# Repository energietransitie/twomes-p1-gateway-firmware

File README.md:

# Twomes P1 Gateway measurement device
Firmware for the Twomes P1 Gateway measurement device.

## Table of contents
* [General info](#general-info)
* [Deploying](#deploying)
* [Pairing satellites](#pairing-satellites) 
* [Developing](#developing)
* [Features](#features)
* [Status](#status)
* [License](#license)
* [Citation](#citation)
* [Credits](#credits)

## General info
This repository contains the firmware for the [Twomes P1 Gateway device](https://github.com/energietransitie/twomes-p1-gateway-hardware). It is written in C and is based on the [ESP-IDF](https://github.com/espressif/esp-idf) platform. It uses the [Generic Firmware for Twomes measurement devices](https://github.com/energietransitie/twomes-generic-esp-firmware) for matters such as device preperation, provisioning of home Wi-Fi network credentials, device-backend activation, network time synchronisation via NTP and secure uploading of measurement data. 

This specific firmware reads data from the P1 port of smart meters adhering to the [DSMR standards](https://www.netbeheernederland.nl/dossiers/slimme-meter-15/documenten). As part of its gateway function, it can be paired with one or more 'satellite' measurement devices, receive measurements via the energy-efficient [ESP-NOW](https://www.espressif.com/en/products/software/esp-now/overview) protocol, thus lengthening the battery life of such satellite measurement devcies, and upload these messages via Wi-Fi and the internet to a Twomes server.

For the associated hardware design files for the P1 Gateway hardware and enclosure and tips and instructions how to produce and assemble the hardware, please see the [twomes-p1-gateway-hardware](https://github.com/energietransitie/twomes-p1-gateway-hardware) repository. 

## Deploying
This section describes how you can deploy binary releases of the firmware, i.e. without changing the source code, without a development environment and without needing to compile the source code.

### Prerequisites
To deploy the firmware, in addition to the [generic prerequisites for deploying Twomes firmware](https://github.com/energietransitie/twomes-generic-esp-firmware#prerequisites), you need:
* a 3.3V TTL-USB Serial Port Adapter (e.g. [FT232RL](https://www.tinytronics.nl/shop/en/communication-and-signals/usb/ft232rl-3.3v-5v-ttl-usb-serial-port-adapter), CP210x, etc..), including the cable to connect ths adapter to a free USB port on your computer (a USB to miniUSB cable in the case of a [FT232RL](https://www.tinytronics.nl/shop/en/communication-and-signals/usb/ft232rl-3.3v-5v-ttl-usb-serial-port-adapter));
* (optional: more stable) Supply 5V DC power to the device via the micro-USB jack of the device.
* Find a row of 6 holes holes (next to the ESP32 on the PCB of the  P1 Gateway), find the `GND` pin (see  bottom of the PCB), align the 6 pins of the serial port adapter such that `GND` and other pins match; then connect the serial port adapter to your computer and connect the 6 pins of the serial port adapter to the 6 holes on the PCB.

### Device preparation step 1: Uploading firmware

* Download the [binary release for your device](https://github.com/energietransitie/twomes-p1-gateway-firmware/releases) and extract it to a directory of your choice.
* If you used the device before, you shoud first [erase all persistenly stored data](https://github.com/energietransitie/twomes-generic-esp-firmware#erasing-all-persistenly-stored-data).
* Follow the [generic Twomes firmware upload instructions ](https://github.com/energietransitie/twomes-generic-esp-firmware#device-preparation-step-1a-uploading-firmware-to-esp32), with the exceptions mentioned below:
	* When you see the beginning of the sequence `Connecting ......_____......`, press and hold the button labeled `GPIO0 (SW2)` on the PCB, then briefly press the button labeled `RESET`, then release the button labeled `GPIO0 (SW2) `;
	* You should see an indication that the firmware is being written to the device.
	* When the upload is finished, view the serial output with a serial monitor tool like [PuTTY](https://www.chiark.greenend.org.uk/~sgtatham/putty/) or the utility of your IDE (115200 baud). Press `RESET (SW1)` shortly to  make sure the firmware boots. 

### Device Preparation step 2 and further 
Please follow the [generic firmware instructions for these steps](https://github.com/energietransitie/twomes-generic-esp-firmware#device-preparation-step-2-establishing-a-device-name-and-device-activation_token). 

## Pairing satellites
Pairing a satellite to the  [Twomes P1 Gateway measurement device](https://github.com/energietransitie/twomes-p1-gateway-firmware) works as follows:
* Place the battery in the satellite module, or remove the [insulatting battery pull tab](https://nl.mouser.com/ProductDetail/Keystone-Electronics/117?qs=sGAEpiMZZMv0NwlthflBi4fkPBGNPNEM5y3HK%252B53UQM%3D), make sure it is near the gateway device to be able to see whether the pairing is successful.
* On the satellite module, shortly press the `RESET (SW1)` button (labeled `R` on the enclosure); A green LED will start blink for 20 seconds to indicate that the satellite module is in pairing mode, i.e. listens (on 2.4 GHz channel 0) to the gateway device telling it which ESP-NOW channel to use after pairing.
* On the gateway device, within these 20 seconds, press the `GPIO12 (SW2)` (labeled `K` on the enclosure, which stands for the Dutch word "Koppelen"). The gateway device now sends, via 2.4 GHz channel 0, which channel the gateway module should use for subsequent ESP-NOW messages. The green LED on the gateway device blinks shortly during this transmission.
* On the satellite module, when the channel number received, the green LED will turn on steady for about 5 seconds.
* This procedure can be repeated if needed (e.g., when the gateway device is connected to the internet via another Wi-Fi network).

## Developing 
This section describes how you can change the source code using a development environment and compile the source code into a binary release of the firmware that can be depoyed, either via the development environment, or via the method described in the section [Deploying](#deploying).

Please see the [developing section of the generic Twomes firmware](https://github.com/energietransitie/twomes-generic-esp-firmware#developing) first. Remember to press buttons to upload the firmware: 
* When you see the beginning of the sequence `Connecting ....___....`, press and hold the button labeled `GPIO0 (SW2)` on the PCB, then briefly press the button labeled `RESET (SW1)`, then release the button labeled `GPIO0 (SW2)`;
* You should see an indication that the firmware is being written to the device.

## Features
List of features ready and TODOs for future development (other than the [features of the generic Twomes firmware](https://github.com/energietransitie/twomes-generic-esp-firmware#features)). 

Ready:
* Read data from the P1 port of devices adhering to DSMRv4 and DSMRv5 (UART settings 115200/8N1).
* Read data from the P1 port of devices adhering to DSMRv2 and DSMRv3 (UART settings 9600/7E1).
* Indicate status and error via LEDs.
* Reset Wi-Fi provisioning by a long press (>10s) of the button `K` (this button is labeled `GPIO12 (SW3)` on the PCB). 
* Confirm pairing with satellite measurement devices with the button `K` (this button is labeled `GPIO12 (SW3)` on the PCB).
* Receive ESP-NOW data from satellite measurement devices and send this to a Twomes server: 
	* [Twomes Boiler Monitor Module](https://github.com/energietransitie/twomes-boiler-monitor-firmware)
	* [Twomes Room Monitor Module](https://github.com/energietransitie/twomes-room-monitor-firmware)  

To-do:
* Align indication of status and error via LEDs with other measurement devices. 

## Status
Project is: in Progress.

## License
This software is available under the [Apache 2.0 license](./LICENSE.md), Copyright 2021 [Research group Energy Transition, Windesheim University of Applied Sciences](https://windesheim.nl/energietransitie) 

## Citation

If you use this repository in your research or work, please cite the following pre-print, which describes the overall NeedForHeat DataGear system of which this repository is a part:

> Ter Hofte, H., & van Ravenzwaaij, N. (2025). *NeedForHeat DataGear: An Open Monitoring System to Accelerate the Residential Heating Transition*. arXiv preprint arXiv:2509.06927. https://doi.org/10.48550/arXiv.2509.06927

**Note:** This is a pre-print submitted on 8 Sep 2025 and has not yet been peer-reviewed. For the full paper, see [https://arxiv.org/abs/2509.06927](https://arxiv.org/abs/2509.06927).

## Credits
This software is a collaborative effort of:
* Sjors Smit ·  [@Shorts1999](https://github.com/Shorts1999)

... with help from the following persons for laying the ground work (see legacy branch for their contributions):
* Fredrik-Otto Lautenbag ·  [@Fredrik1997](https://github.com/Fredrik1997)
* Gerwin Buma ·  [@GerwinBuma](https://github.com/GerwinBuma) 
* Werner Heetebrij ·  [@Werner-Heetebrij] (https://github.com/Werner-Heetebrij)
* Henri ter Hofte · [@henriterhofte](https://github.com/henriterhofte)

... and with help from the following persons for bugfixes:
* Marco Winkelman · [@MarcoW71](https://github.com/MarcoW71)
* Kevin Janssen · [@KevinJan18](https://github.com/KevinJan18)

We use and gratefully acknowlegde the efforts of the makers of the following source code and libraries:
* [ESP-IDF](https://github.com/espressif/esp-idf), by Espressif Systems, licensed under [Apache 2.0 License](https://github.com/espressif/esp-idf/blob/master/LICENSE)

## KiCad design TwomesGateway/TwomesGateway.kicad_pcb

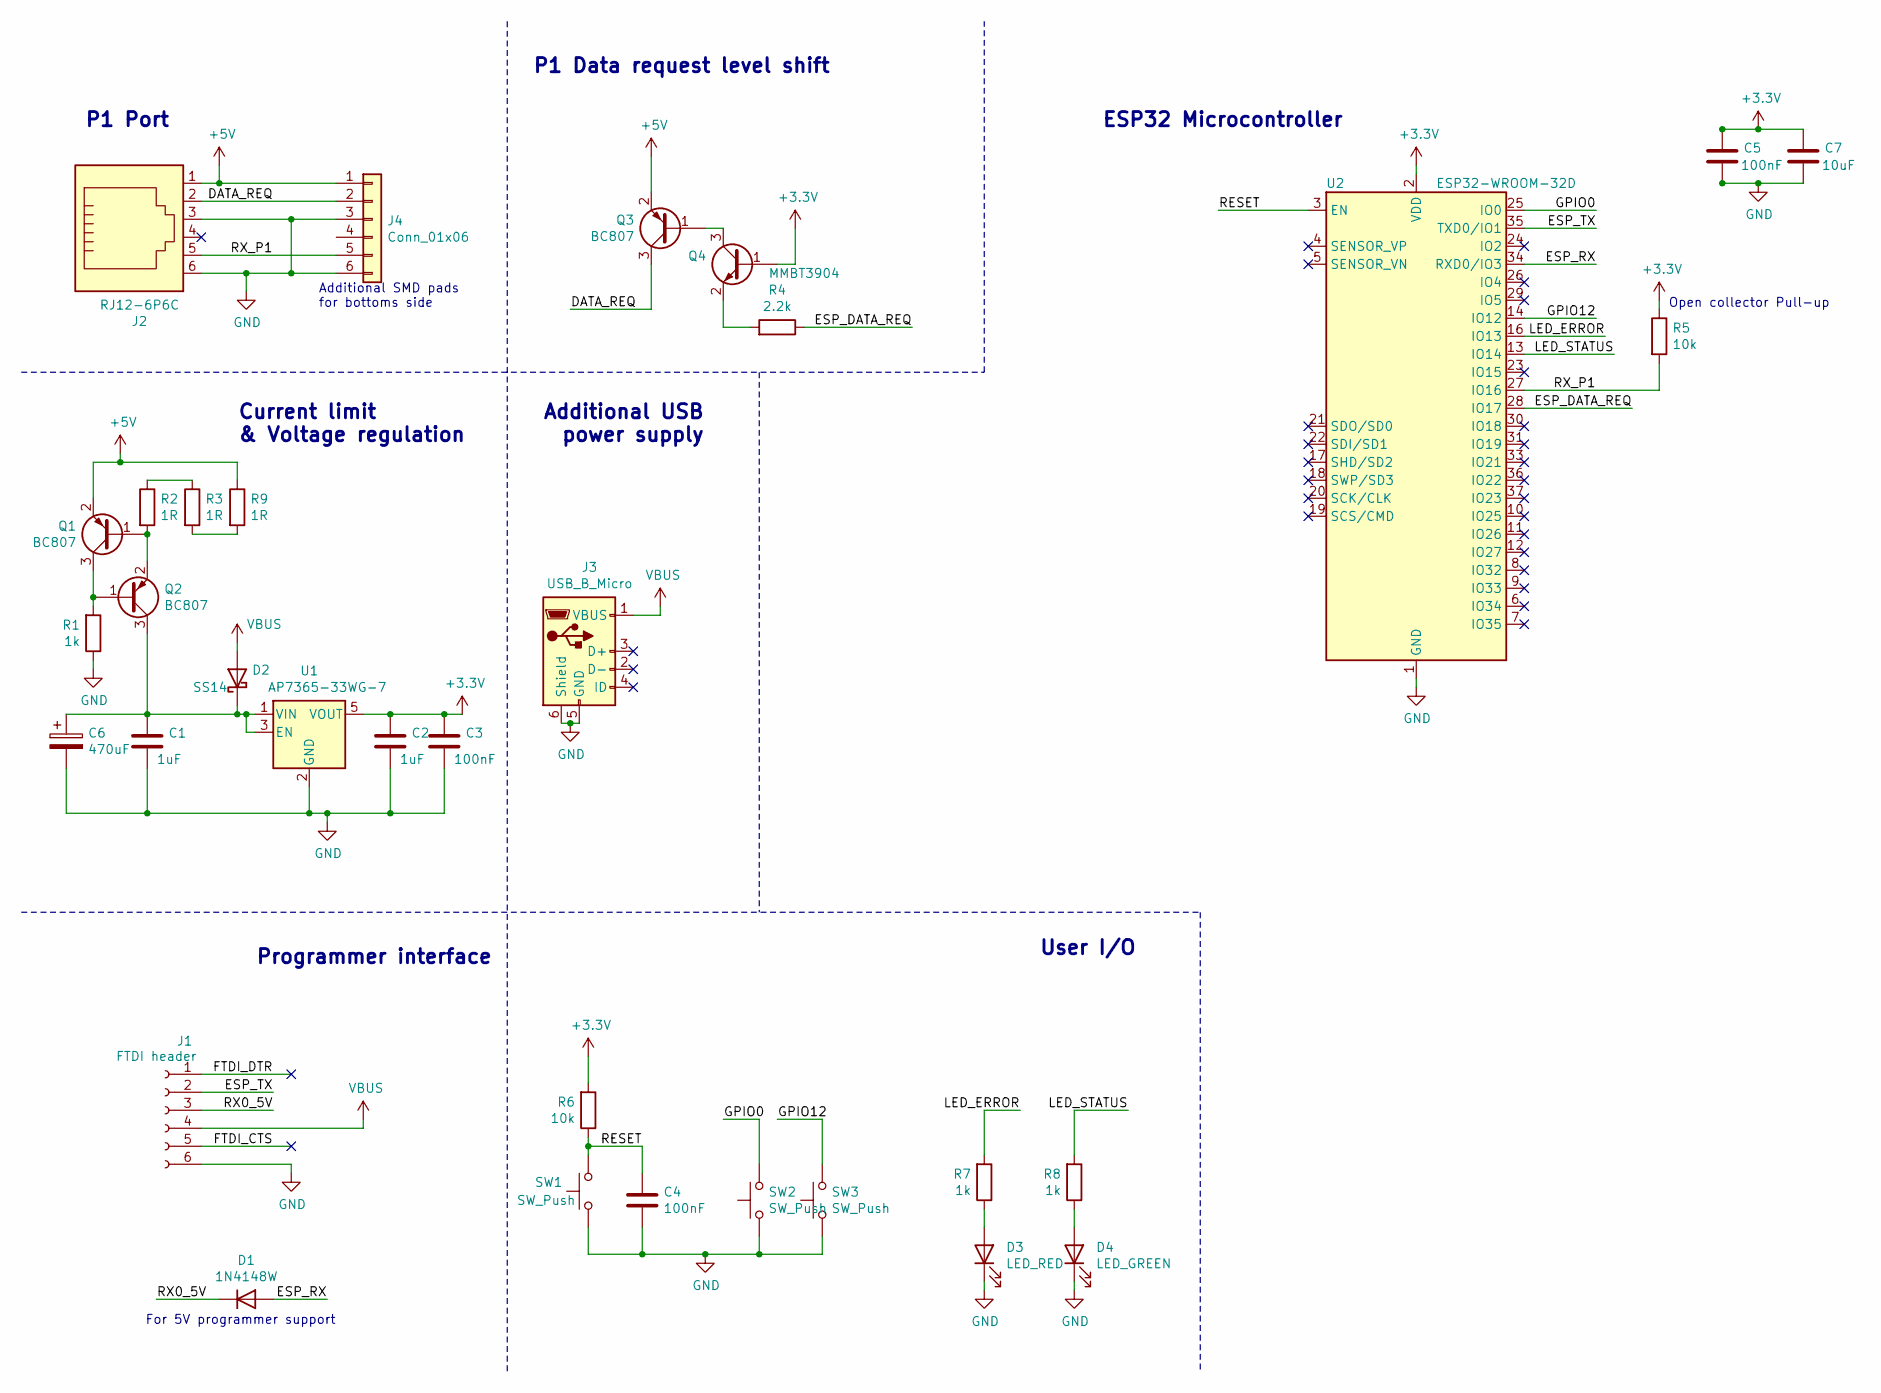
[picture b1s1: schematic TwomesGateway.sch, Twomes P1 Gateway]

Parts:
C1, C2: 1uF; C_0603_1608Metric
C3, C4, C5: 100nF; C_0603_1608Metric
C6: 470uF; CP_Elec_8x10.5
C7: 10uF; C_0603_1608Metric
D1: 1N4148W; D_SOD-123
D2: SS14; D_SOD-123
D3: LED_RED; LED_1206_3216Metric
D4: LED_GREEN; D_0805_2012Metric
J1: FTDI header; PinHeader_1x06_P2.54mm_Vertical
J2: RJ12-6P6C; RJ12_Amphenol_54601
J3: USB_B_Micro; ÙSB_JLC__SHOUHAN_microQTJ
J4: Conn_01x06; Rj12SMD
Q1, Q2, Q3: BC807; SOT-23
Q4: MMBT3904; SOT-23
R1, R7, R8: 1k; R_0603_1608Metric
R2, R3, R9: 1R; R_0603_1608Metric
R4: 2.2k; R_0603_1608Metric
R5, R6: 10k; R_0603_1608Metric
SW1, SW2, SW3: SW_Push; SW_Push_1P1T_NO_6x6mm_H9.5mm
U1: AP7365-33WG-7; SOT-23-5
U2: ESP32-WROOM-32D; ESP32-WROOM-32

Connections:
+3V3: C2.1, C3.1, C5.1, C7.1, Q4.1 (B), R5.1, R6.2, U1.5 (VOUT), U2.2 (VDD)
+5V: J2.1, J4.1, Q1.2 (E), Q3.2 (E), R9.1
/DATA_REQ: J2.2, J4.2, Q3.3 (C)
/ESP_DATA_REQ: R4.1, U2.28 (IO17)
/ESP_RX: D1.2 (A), U2.34 (RXD0/IO3)
/ESP_TX: J1.2, U2.35 (TXD0/IO1)
/FTDI_CTS: J1.5
/FTDI_DTR: J1.1
/GPIO0: SW2.2, U2.25 (IO0)
/GPIO12: SW3.2, U2.14 (IO12)
/LED_ERROR: R7.2, U2.16 (IO13)
/LED_STATUS: R8.2, U2.13 (IO14)
/RESET: C4.1, R6.1, SW1.2, U2.3 (EN)
/RX0_5V: D1.1 (K), J1.3
/RX_P1: J2.5, J4.5, R5.2, U2.27 (IO16)
GND: C1.2, C2.2, C3.2, C4.2, C5.2, C6.2, C7.2, D3.1 (K), D4.1 (K), J1.6, J2.3, J2.6, J3.5 (GND), J3.6 (Shield), J4.3, J4.6, R1.1, SW1.1, SW2.1, SW3.1, U1.2 (GND), U2.1 (GND), U2.15 (GND), U2.38 (GND), U2.39 (GND)
unnamed: C1.1, C6.1, D2.1 (K), Q2.3 (C), U1.1 (VIN), U1.3 (EN)
unnamed: D3.2 (A), R7.1
unnamed: D4.2 (A), R8.1
unnamed: Q1.1 (B), Q2.2 (E), R2.2
unnamed: Q1.3 (C), Q2.1 (B), R1.2
unnamed: Q3.1 (B), Q4.3 (C)
unnamed: Q4.2 (E), R4.2
unnamed: R2.1, R3.1
unnamed: R3.2, R9.2
VBUS: D2.2 (A), J1.4, J3.1 (VBUS)

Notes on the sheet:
Current limit & Voltage regulation
P1 Port
Programmer interface
For 5V programmer support
Additional USB power supply
P1 Data request level shift
Open collector Pull-up
ESP32 Microcontroller
User I/O
Additional SMD pads for bottoms side

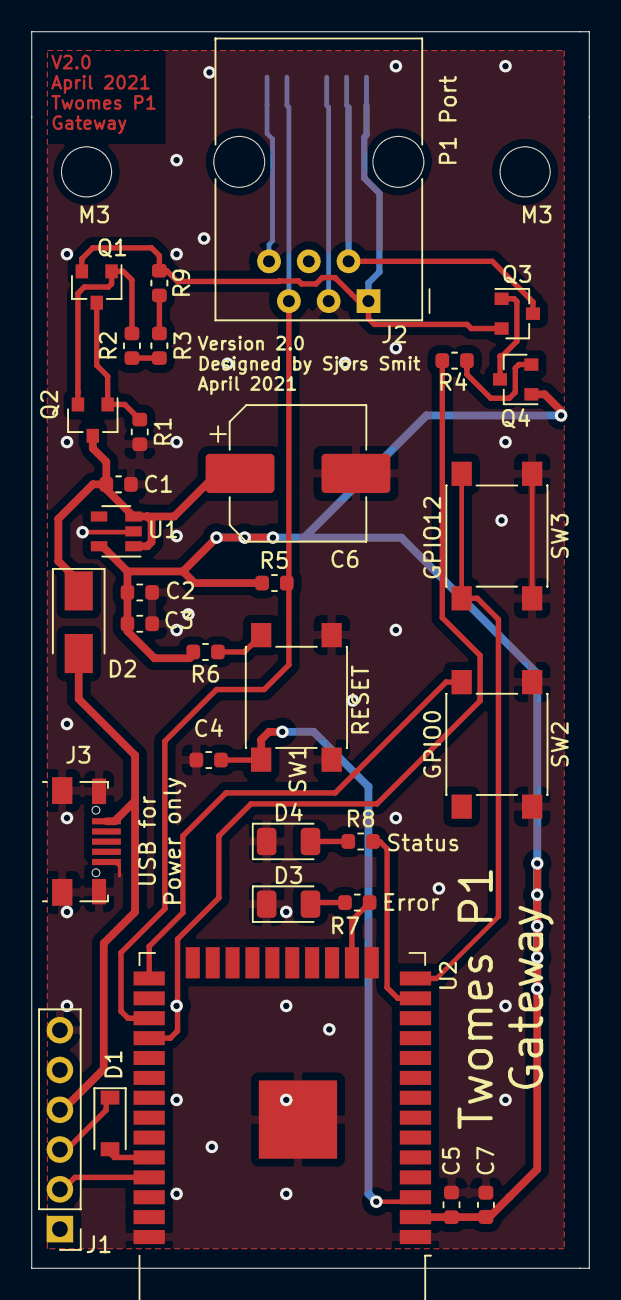
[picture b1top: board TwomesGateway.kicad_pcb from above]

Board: 2 copper layers, 35.6 x 79.0 mm, 35 parts (1 on the bottom side), 24 nets.

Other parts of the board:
M3, M3#2: MountingHole_3.2mm_M3

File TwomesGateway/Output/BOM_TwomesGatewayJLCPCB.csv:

"Column1;Column2;Column3;Column4"
"Comment;Designator;Footprint;LCSC"
"1uF;C1,C2;Capacitor_SMD:C_0603_1608Metric;C15849"
"100nF;C3,C4,C5;Capacitor_SMD:C_0603_1608Metric;C14663"
"1000uF;C6;Capacitor_SMD:CP_Elec_8x10.5;C134755"
"1N4148W;D1;Diode_SMD:D_SOD-123;C81598 "
"CUS10S30;D2;Diode_SMD:D_SOD-123;C146335 "
"LED_RED;D3;LED_SMD:LED_1206_3216Metric;C84256"
"LED_GREEN;D4;Diode_SMD:D_0805_2012Metric;C2297"
"FTDI header;J1;Connector_PinHeader_2.54mm:PinHeader_1x06_P2.54mm_Vertical;DO NOT PLACE"
"RJ12-6P6C;J2;Connector_RJ:RJ12_Amphenol_54601;DO NOT PLACE"
"USB_B_Micro;J3;Connector_USB:USB_Micro-B-SHOUHAN_QTJ;C404968"
"BC807;Q1,Q2,Q3;Package_TO_SOT_SMD:SOT-23;C82369"
"MMBT3904;Q4;Package_TO_SOT_SMD:SOT-23;C20526"
"1k;R1,R7,R8;Resistor_SMD:R_0603_1608Metric;C21190"
"1R;R2,R3,R9;Resistor_SMD:R_0603_1608Metric;C22936"
"2.2k;R4;Resistor_SMD:R_0603_1608Metric;C4190"
"10k;R5,R6;Resistor_SMD:R_0603_1608Metric;C25804"
"SW_Push;SW1,SW2,SW3;Button_Switch_SMD:SW_Push_1P1T_NO_6x6mm_H9.5mm;C83206"
"AP7365-33WG-7;U1;Package_TO_SOT_SMD:SOT-23-5;C150742"
"ESP32-WROOM-32E;U2;RF_Module:ESP32-WROOM-32;C701343"

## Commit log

2020-10-27 init
2020-11-04 code optimization
2020-11-06 Solved wrong timeRead readout
2020-11-06 Removed JSON library
2020-11-06 updated dependencies
2020-12-06 added pdf file
2020-12-16 Update pins and added TCP debugging
2020-12-17 Commented wifi client and post request
2021-01-08 added JSON library
2021-01-08 used prettier formatter, added JSON library, made sender function with defined send modes, saved connection params in struct and used defined params from utils.h, wrote environment for collecting all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
2021-01-08 updated: example for utils.h
2021-01-12 bug fix in checkValues function, tested this code with online VPS; test succeed!
2021-01-19 "Removed unnecessary code"
2021-01-21 Removed hardware files and changed loop in code
2021-01-21 Changed smartMeter values
2021-01-21 used code formatter
2021-01-21 Manual merge from esp_now_receiver: added espnow_setting file
2021-01-21 Manual merge from esp_now_receiver: configured ESPNOW, made system for standarized data saving from all sources(smartMeter, roomTemp and boilerTemp), made WiFiconfig and ESPnow function. This is not 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
2021-01-21 modified existing send and parse functions to new data management, but bug with global last actions variable needs attention, not everything in main is usable with new functions
2021-01-22 made caching sytem operational, smartMeter functions needs attention, cleaned code, tested monitor/ESPNOW support;positive, tested backOffice support;positive
2021-01-22 add BLE settings file
2021-01-22 merged BLE support from BLE_design branch
2021-01-22 uncomment this for 8MB flash support
2021-01-22 made smartMeter function compatible with caching system
2021-01-22 updated readme and comments
2021-01-22 upd. name
2021-01-22 fix BLE config header doc
2021-01-22 upd. comment improvement
2021-01-22 cleaned function declaration
2021-04-07 Create LICENSE
2021-05-18 Hardware
2021-05-21 CO2 support in JSON packaging
2021-05-27 Longpress erases only Wifi config
2021-05-27 Switch to BLE provisioning
2021-05-27 Update to new version
2021-06-01 Cleanup to reupload with only needed files
2021-06-01 Add P1 reading and parsing. Move functions to library
2021-06-01 Update to 16MB Flash size
2021-06-01 Read eMeter Timestamp and gMeter timestamp
2021-06-04 HTTPS POST support test API + JSON bugfix
2021-06-10 Add support for sensor pairing
2021-06-15 P1 Port Backoffice upload, GenericV1.7.3
2021-06-22 Gateway Manuals initial Draft (NOT FINISHED)
2021-06-22 Remove defined upload port
2021-06-22 Updated to 16MB
2021-06-28 Complete manuals. Added video
2021-06-28 Update to new Twomes youtube Channel
2021-06-28 Update index.html
    corrected error in link to second video
2021-06-28 Update index.html
    improved fix
2021-06-28 Update index.html
    removed disclaimer
2021-06-28 Update index.html
    remove WarmteWachter video; not needed in app (was just an illustration)
2021-06-28 Delete example.png
    no longer needed
2021-06-29 Hardware moved to separate repository
2021-07-09 Update README.md
    refer to hadware repo; rearrange credits a bit to fit better with other repos
2021-09-15 Set fixed version 3.2.0
2021-10-03 Incorporate wireless_802_11_mutex to switch between ESP-now and Wifi
2021-10-07 update to wifi_connect and disconnect functions
2021-10-10 remove debug loop
    A while(buttonP2) loop was added at boot for debugging (seeing when a device crashed during long term test runs) was left inside the source code.
2021-10-14 Added proper JSON for CO2 sensor
2021-10-20 Add conversion for SCD41 RH and T
2021-10-21 update to new generic firmware
2021-10-26 Remove manual connect/disconnect
2021-10-28 Quick test fix, longer P1 read
2021-10-29 Turn log level from debug to info
2021-10-29 fix upload.bat offset
2021-10-29 no more than 3 decimals in P1-meter readings
2021-11-03 Create a DSMR2.2 version: 9600 7N1 no CRC
2021-11-03 Fix DSMR2.2 UART configuration
2021-11-04 Script to auto-create release for all devicetypes
2021-11-04 update readme to reflect new build method
2021-11-04 align with generic firmware
2021-11-04 Update README.md
    remove channel and MAC provisioning as separate item on feature list (this is part of pairing)
2021-11-04 Update README.md
    added generic info about pairing satellites
2021-11-05 0x8000 compatibility
2021-11-05 Larger message size
2021-11-05 DSMR2.2 specific parsing of gas parameters added
2021-11-05 SinlgeButton-Align-Generic-Firmware
2021-11-06 single button operation aligned with generic firmware
2021-11-06 allign button constants naming with other repos
2021-11-07 improve message and buffer size include sdkconfig updates
2021-11-25 add presence detection
2021-11-25 works bit not _yet_ with presence detection
2021-11-26 fixed boot startup interval
2021-12-01 Update defines for production server
2021-12-04 fixed typo
2021-12-04 fixed long-button-press handling
2021-12-07 SourceFiles used kleine uitrol
2021-12-11 fix delay before restart after long button presse and use delete_bearer
2021-12-11 now including esp_wifi_restore()
2021-12-11 fixed timestamps DSMR2OR3
2021-12-24 bump manuals to version used for big rollout in Assendorp
2021-12-24 add faq items
2021-12-27 restructure manual directory; platformio.ini in production mode
2021-12-29 fix typo
2022-03-18 bump config to testserver
2022-03-31 link fix
